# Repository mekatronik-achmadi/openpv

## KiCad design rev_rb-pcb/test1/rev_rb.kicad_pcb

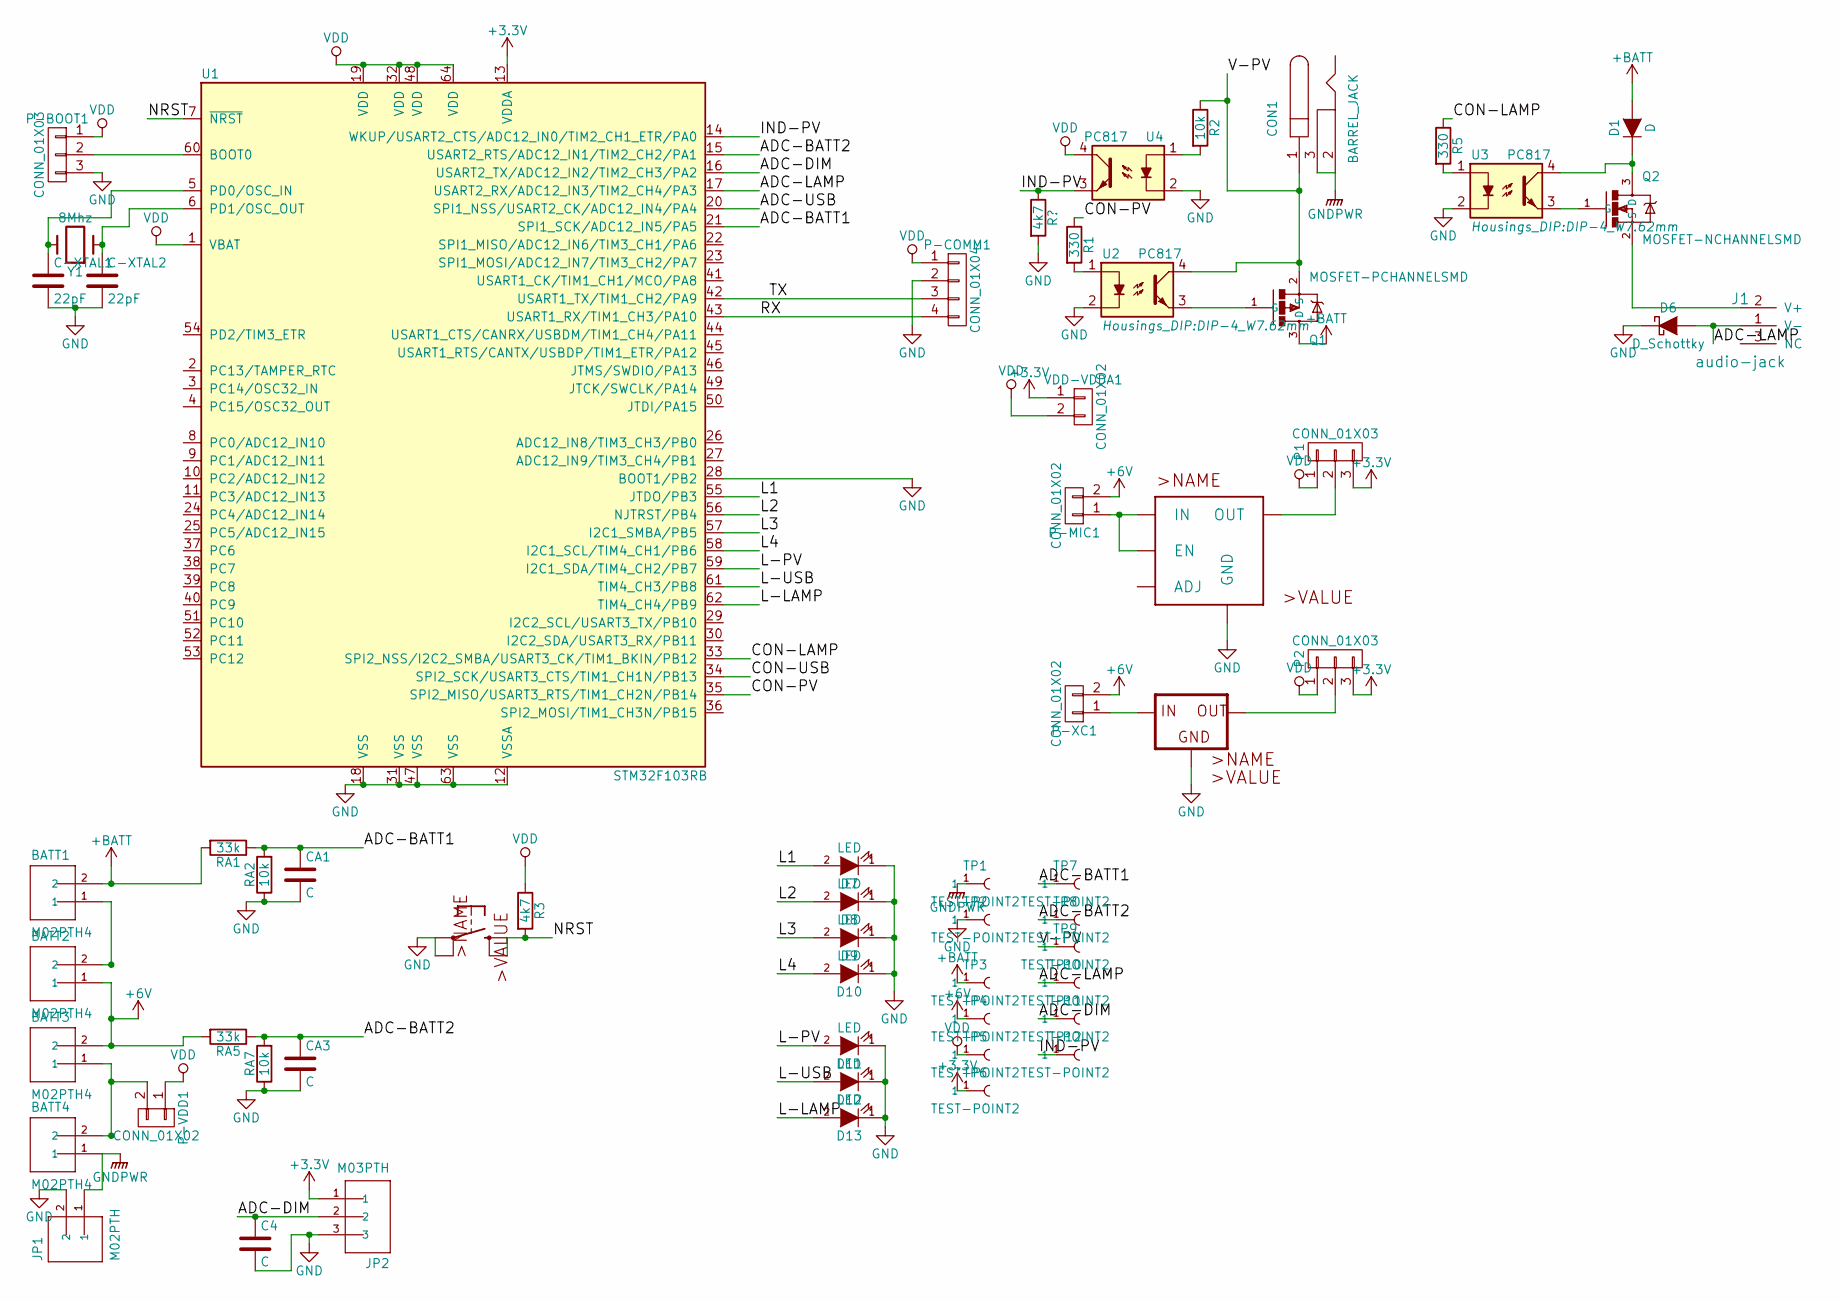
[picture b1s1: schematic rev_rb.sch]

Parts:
BATT1, BATT2, BATT3, BATT4: M02PTH4; SparkFun-1X02_XTRA_BIG
C4: C; C_0805
C-XTAL1, C-XTAL2: 22pF; C_0805
CA1, CA3: C; C_0805
CON1: BARREL_JACK; JACK_ALIM
D1: D; SMA_Standard
D6: D_Schottky; SMA_Standard
D7, D8, D9, D10, D11, D12, D13: LED; LED-0805
J1: audio-jack; JACK_LAPAN
JP1: M02PTH; SparkFun-1X02_XTRA_BIG
JP2: M03PTH; SparkFun-1X03_LONGPADS
P1, P2: CONN_01X03; Pin_Header_Straight_1x03
P-BOOT1: CONN_01X03; Pin_Header_Straight_1x03
P-COMM1: CONN_01X04; Pin_Header_Straight_1x04
P-MIC1: CONN_01X02; Pin_Header_Straight_1x02
P-VDD1: CONN_01X02; Pin_Header_Straight_1x02
P-XC1: CONN_01X02; Pin_Header_Straight_1x02
Q1: MOSFET-PCHANNELSMD; TO-220
Q2: MOSFET-NCHANNELSMD; TO-220
R1, R5: 330; R_0805
R2: 10k; R_0805
R3: 4k7; R_0805
RA1, RA5: 33k; R_0805
RA2, RA7: 10k; R_0805
TP1, TP2, TP3, TP4, TP5, TP6, TP7, TP8, TP9, TP10, TP11, TP12: TEST-POINT2; SparkFun-PAD.03X.05
U1: STM32F103RB; TQFP-64_10x10mm_Pitch0.5mm
U2, U3, U4: PC817; DIP-4_W7.62mm
U6: 10-XX_B3F-10XX; B3F-10XX
U7: MIC5219BM5_SOT23-5; SOT-23-5
U8: XC63FPM_SOT23; SOT-23
VDD-VDDA1: CONN_01X02; Pin_Header_Straight_1x02
Y1: 8Mhz; HC-49V

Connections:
+3V3: JP2.1, P1.3, P2.3, TP6.1, U1.13 (VDDA), VDD-VDDA1.1
+6V: BATT2.1, BATT3.2, P-MIC1.2, P-XC1.2, RA5.2, TP4.1
+BATT: BATT1.2, D1.2 (A), Q1.3 (D), RA1.2, TP3.1
/ADC-BATT1: CA1.1, RA1.1, RA2.2, TP7.1, U1.21 (SPI1_SCK/ADC12_IN5/PA5)
/ADC-BATT2: CA3.1, RA5.1, RA7.2, TP8.1, U1.15 (USART2_RTS/ADC12_IN1/TIM2_CH2/PA1)
/ADC-DIM: C4.1, JP2.2, TP11.1, U1.16 (USART2_TX/ADC12_IN2/TIM2_CH3/PA2)
/ADC-LAMP: D6.2 (A), J1.1 (V-), TP10.1, U1.17 (USART2_RX/ADC12_IN3/TIM2_CH4/PA3)
/ADC-USB: U1.20 (SPI1_NSS/USART2_CK/ADC12_IN4/PA4)
/CON-LAMP: R5.1, U1.33 (SPI2_NSS/I2C2_SMBA/USART3_CK/TIM1_BKIN/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)
/CON-PV: R1.1, U1.35 (SPI2_MISO/USART3_RTS/TIM1_CH2N/PB14)
/CON-USB: U1.34 (SPI2_SCK/USART3_CTS/TIM1_CH1N/PB13)
/IND-PV: TP12.1, U1.14 (WKUP/USART2_CTS/ADC12_IN0/TIM2_CH1_ETR/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), U4.3
/L1: D7.2 (A), U1.55 (JTDO/PB3)
/L2: D8.2 (A), U1.56 (NJTRST/PB4)
/L3: D9.2 (A), U1.57 (I2C1_SMBA/PB5)
/L4: D10.2 (A), U1.58 (I2C1_SCL/TIM4_CH1/PB6)
/L-LAMP: D13.2 (A), U1.62 (TIM4_CH4/PB9)
/L-PV: D11.2 (A), U1.59 (I2C1_SDA/TIM4_CH2/PB7)
/L-USB: D12.2 (A), U1.61 (TIM4_CH3/PB8)
/NRST: R3.2, U1.7 (~NRST), U6.1 (S), U6.2 (S1)
/RX: P-COMM1.4, U1.43 (USART1_RX/TIM1_CH3/PA10)
/TX: P-COMM1.3, U1.42 (USART1_TX/TIM1_CH2/PA9)
/V-PV: CON1.1, Q1.2 (S), R2.1, TP9.1, U2.4
GND: C4.2, C-XTAL1.2, C-XTAL2.2, CA1.2, CA3.2, D6.1 (K), D7.1 (K), D8.1 (K), D9.1 (K), D10.1 (K), D11.1 (K), D12.1 (K), D13.1 (K), JP1.2, JP2.3, P-BOOT1.3, P-COMM1.2, RA2.1, RA7.1, TP2.1, U1.12 (VSSA), U1.18 (VSS), U1.28 (BOOT1/PB2), U1.31 (VSS), U1.47 (VSS), U1.63 (VSS), U2.2, U3.2, U4.2, U6.3, U6.4 (P1), U7.2 (GND), U8.1 (GND)
GNDPWR: BATT4.1, CON1.2, CON1.3, JP1.1, TP1.1
unnamed: BATT1.1, BATT2.2
unnamed: BATT3.1, BATT4.2, P-VDD1.2
unnamed: C-XTAL1.1, U1.5 (PD0/OSC_IN), Y1.2
unnamed: C-XTAL2.1, U1.6 (PD1/OSC_OUT), Y1.1
unnamed: D1.1 (K), Q2.3 (D), U3.4
unnamed: J1.2 (V+), Q2.2 (S)
unnamed: P1.2, U7.5 (OUT)
unnamed: P2.2, U8.2 (OUT)
unnamed: P-BOOT1.2, U1.60 (BOOT0)
unnamed: P-MIC1.1, U7.1 (IN), U7.3 (EN)
unnamed: P-XC1.1, U8.3 (IN)
unnamed: Q1.1 (G), U2.3
unnamed: Q2.1 (G), U3.3
unnamed: R1.2, U2.1
unnamed: R2.2, U4.1
unnamed: R5.2, U3.1
VDD: P1.1, P2.1, P-BOOT1.1, P-COMM1.1, P-VDD1.1, R3.1, TP5.1, U1.1 (VBAT), U1.19 (VDD), U1.32 (VDD), U1.48 (VDD), U1.64 (VDD), U4.4, VDD-VDDA1.2

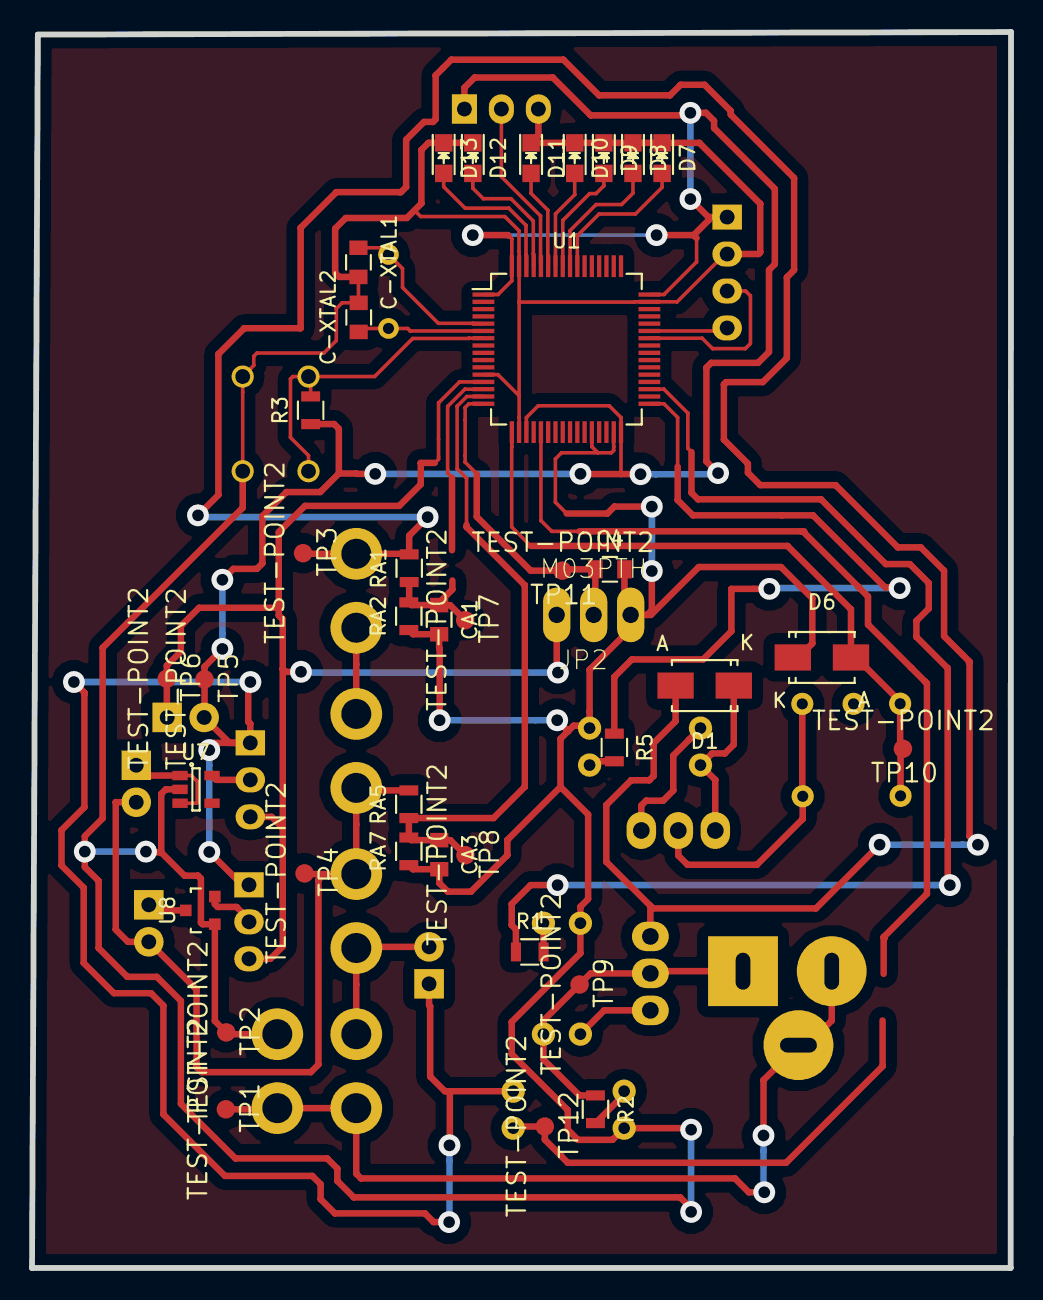
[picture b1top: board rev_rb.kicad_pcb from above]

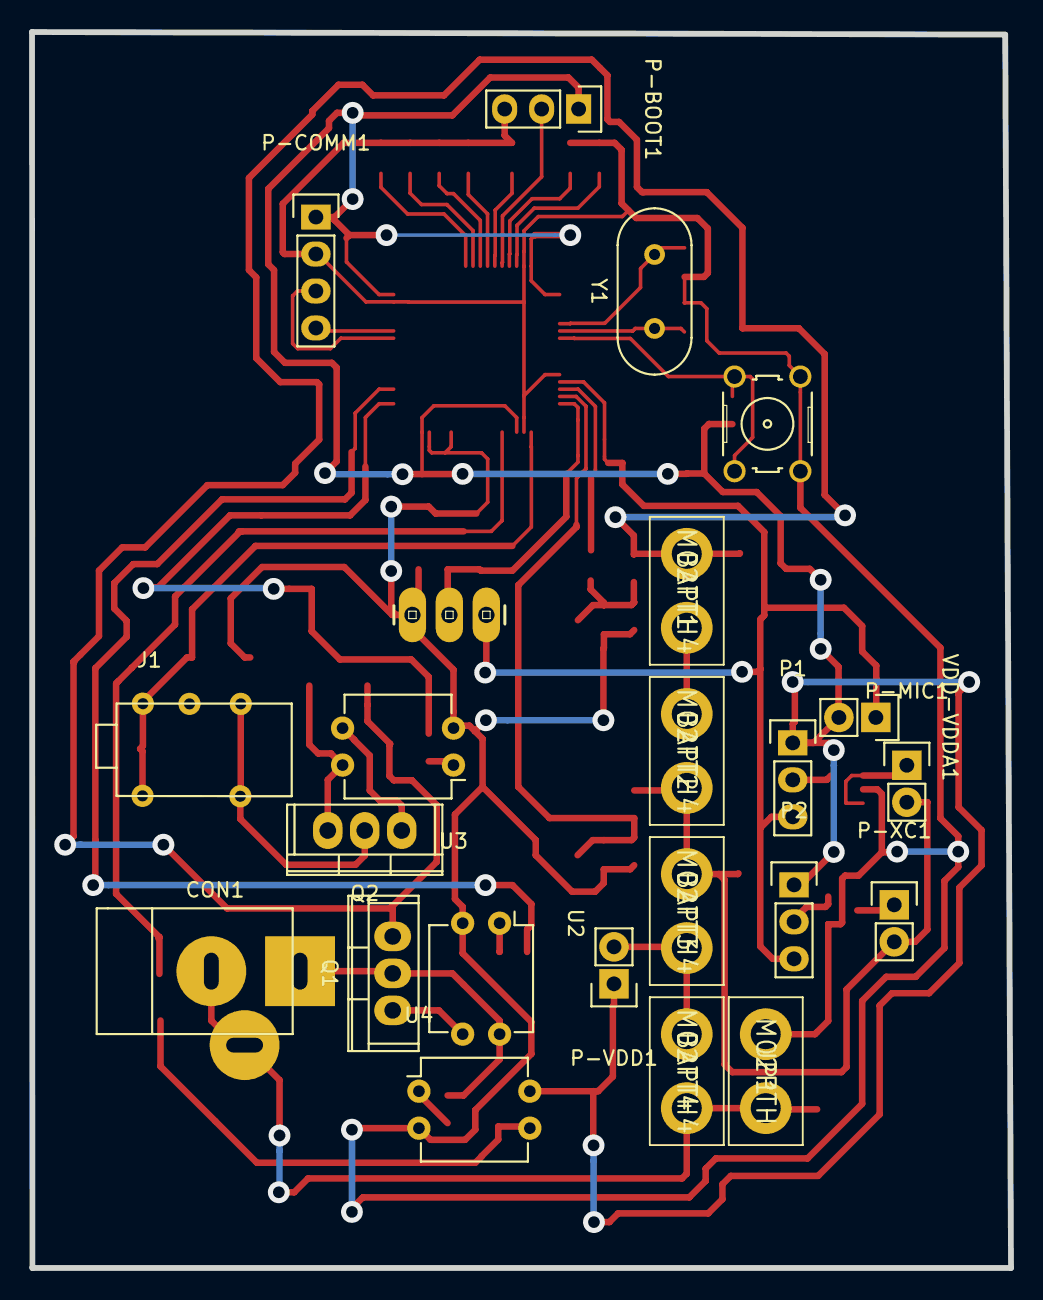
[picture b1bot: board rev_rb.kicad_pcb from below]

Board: 2 copper layers, 67.2 x 84.9 mm, 60 parts (23 on the bottom side), 40 nets.

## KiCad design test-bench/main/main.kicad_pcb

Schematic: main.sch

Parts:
C-REG1, C-REG2: 100uF 50v; C_Radial_D5_L6_P2.5
CON-REG1: BARREL_JACK; JACK_ALIM
D1, D2, D3, D4: LED; LED-3MM
D-REG1: D; Diode_DO-35_SOD27_Horizontal_RM10
D-RTC1, D-RTC2: D; Diode_DO-35_SOD27_Horizontal_RM10
DS-REG1: D_Schottky; Diode_DO-35_SOD27_Horizontal_RM10
DZ-REG1: 5v6; Diode_DO-35_SOD27_Horizontal_RM10
IC1: ATMEGA128-A; TQFP-64_14x14mm_Pitch0.8mm
L-REG1: INDUCTOR; INDUCTOR_V
P-ASP1: CONN_01X06; Pin_Header_Straight_1x06
P-LAMP1, P-LAMP2, P-LAMP3, P-LAMP4, P-LAMP5, P-LAMP6, P-LAMP7, P-LAMP8: CONN_02X08; Pin_Header_Straight_2x08
P-RTCBATT1: CONN_01X02; Pin_Header_Straight_1x02
P-UART1: CONN_01X04; Pin_Header_Straight_1x04
R-DISP1, R-DISP2, R-DISP3, R-DISP4, R-DISP5, R-DISP6, R-DISP7: 330; Resistor_Horizontal_RM10mm
R-LED1, R-LED2, R-LED3, R-LED4: 330; Resistor_Horizontal_RM10mm
R-RST1: 4k7; Resistor_Horizontal_RM10mm
R-RTC1, R-RTC2: 4k7; Resistor_Horizontal_RM10mm
U1: 4511N_DIL16; DIP-16_W7.62mm_LongPads
U2: LM2596S_TO263-5; TO-263-5Lead
U3: PCF8563; SOIJ-8_5.3x5.3mm_Pitch1.27mm
Y1: 32khz; Crystal_Watch

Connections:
/D1-A: IC1.61 (PF0(ADC0)), P-LAMP1.15
/D1-B: IC1.60 (PF1(ADC1)), P-LAMP1.13
/D1-C: IC1.59 (PF2(ADC2)), P-LAMP1.11
/D2-A: IC1.58 (PF3(ADC3)), P-LAMP2.15
/D2-B: IC1.57 (PF4(ADC4/TCK)), P-LAMP2.13
/D2-C: IC1.56 (PF5(ADC5/TMS)), P-LAMP2.11
/D3-A: IC1.7 (PE5(OC3C/INT5)), P-LAMP3.11
/D3-B: IC1.8 (PE6(T3/INT6)), P-LAMP3.13
/D3-C: IC1.9 (PE7(IC3/INT7)), P-LAMP3.15
/D4-A: IC1.47 ((AD4)PA4), P-LAMP4.15
/D4-B: IC1.46 ((AD5)PA5), P-LAMP4.13
/D4-C: IC1.45 ((AD6)PA6), P-LAMP4.11
/D5-A: IC1.44 ((AD7)PA7), P-LAMP5.15
/D5-B: IC1.43 (PG2(ALE)), P-LAMP5.13
/D5-C: IC1.42 ((A15)PC7), P-LAMP5.11
/D6-A: IC1.41 ((A14)PC6), P-LAMP6.15
/D6-B: IC1.40 ((A13)PC5), P-LAMP6.13
/D6-C: IC1.39 ((A12)PC4), P-LAMP6.11
/D6-D: IC1.38 ((A11)PC3), P-LAMP6.9
/D7-A: IC1.37 ((A10)PC2), P-LAMP7.15
/D7-B: IC1.36 ((A9)PC1), P-LAMP7.13
/D7-C: IC1.35 ((A8)PC0), P-LAMP7.11
/D7-D: IC1.34 (PG1(~RD~)), P-LAMP7.9
/D8-A: IC1.29 ((ICP1)PD4), P-LAMP8.9
/D8-B: IC1.30 ((XCK1)PD5), P-LAMP8.11
/D8-C: IC1.31 ((T1)PD6), P-LAMP8.13
/D8-D: IC1.32 ((T2)PD7), P-LAMP8.15
/IA: IC1.51 ((AD0)PA0), U1.7 (IA)
/IB: IC1.50 ((AD1)PA1), U1.1 (IB)
/IC: IC1.49 ((AD2)PA2), U1.2 (IC)
/ID: IC1.48 ((AD3)PA3), U1.6 (ID)
/LA: P-LAMP1.10, P-LAMP2.10, P-LAMP3.10, P-LAMP4.10, P-LAMP5.10, P-LAMP6.10, P-LAMP7.10, P-LAMP8.10, R-DISP1.1
/LB: P-LAMP1.8, P-LAMP2.8, P-LAMP3.8, P-LAMP4.8, P-LAMP5.8, P-LAMP6.8, P-LAMP7.8, P-LAMP8.8, R-DISP2.1
/LC: P-LAMP1.6, P-LAMP2.6, P-LAMP3.6, P-LAMP4.6, P-LAMP5.6, P-LAMP6.6, P-LAMP7.6, P-LAMP8.6, R-DISP3.1
/LD: P-LAMP1.4, P-LAMP2.4, P-LAMP3.4, P-LAMP4.4, P-LAMP5.4, P-LAMP6.4, P-LAMP7.4, P-LAMP8.4, R-DISP4.1
/LE: P-LAMP1.2, P-LAMP2.2, P-LAMP3.2, P-LAMP4.2, P-LAMP5.2, P-LAMP6.2, P-LAMP7.2, P-LAMP8.2, R-DISP5.1
/LF: P-LAMP1.14, P-LAMP2.14, P-LAMP3.14, P-LAMP4.14, P-LAMP5.14, P-LAMP6.14, P-LAMP7.14, P-LAMP8.14, R-DISP6.1
/LG: P-LAMP1.12, P-LAMP2.12, P-LAMP3.12, P-LAMP4.12, P-LAMP5.12, P-LAMP6.12, P-LAMP7.12, P-LAMP8.12, R-DISP7.1
/MISO: IC1.2 (PE0(RXD0/PDI)), P-ASP1.6
/MOSI: IC1.3 (PE1(TXD0/PDO)), P-ASP1.5
/RST: IC1.20 (~RESET), P-ASP1.3, R-RST1.2
/RTC-SCL: IC1.25 ((SCL/INT0)PD0), R-RTC2.2, U3.6 (SCL)
/RTC-SDA: IC1.26 ((SDA/INT1)PD1), R-RTC1.2, U3.5 (SDA)
/RUN: D2.1 (K), IC1.10 ((~SS~)PB0)
/RX: D3.1 (K), IC1.28 ((TXD1/INT3)PD3), P-UART1.3
/SCK: IC1.11 ((SCK)PB1), P-ASP1.4
/TX: D4.1 (K), IC1.27 ((RXD1/INT2)PD2), P-UART1.4
GND: C-REG1.2, C-REG2.2, CON-REG1.2, CON-REG1.3, D1.1 (K), DS-REG1.2 (A), DZ-REG1.2 (A), IC1.22 (GND), IC1.53 (GND), IC1.63 (AGND), P-ASP1.2, P-LAMP1.16, P-LAMP2.16, P-LAMP3.16, P-LAMP4.16, P-LAMP5.16, P-LAMP6.16, P-LAMP7.16, P-LAMP8.16, P-RTCBATT1.2, P-UART1.2, U1.5 (LE), U1.8 (VSS), U2.3 (GND), U2.5 (!ON!/OFF), U3.4 (VSS)
unnamed: C-REG1.1, D-REG1.1 (K), U2.1 (VIN)
unnamed: CON-REG1.1, D-REG1.2 (A)
unnamed: D1.2 (A), R-LED1.2
unnamed: D2.2 (A), R-LED2.2
unnamed: D3.2 (A), R-LED3.2
unnamed: D4.2 (A), R-LED4.2
unnamed: D-RTC1.1 (K), D-RTC2.1 (K), U3.8 (VDD)
unnamed: D-RTC2.2 (A), P-RTCBATT1.1
unnamed: DS-REG1.1 (K), L-REG1.2, U2.2 (OUT)
unnamed: R-DISP1.2, U1.13 (A)
unnamed: R-DISP2.2, U1.12 (B)
unnamed: R-DISP3.2, U1.11 (C)
unnamed: R-DISP4.2, U1.10 (D)
unnamed: R-DISP5.2, U1.9 (E)
unnamed: R-DISP6.2, U1.15 (F)
unnamed: R-DISP7.2, U1.14 (G)
unnamed: U3.1 (OSCI), Y1.1
unnamed: U3.2 (OSCO), Y1.2
VCC: C-REG2.1, D-RTC1.2 (A), DZ-REG1.1 (K), IC1.21 (VCC), IC1.52 (VCC), IC1.64 (AVCC), L-REG1.1, P-ASP1.1, P-LAMP1.1, P-LAMP2.1, P-LAMP3.1, P-LAMP4.1, P-LAMP5.1, P-LAMP6.1, P-LAMP7.1, P-LAMP8.1, P-UART1.1, R-LED1.1, R-LED2.1, R-LED3.1, R-LED4.1, R-RST1.1, R-RTC1.1, R-RTC2.1, U1.3 (LT), U1.4 (BI), U1.16 (VDD), U2.4 (FB)

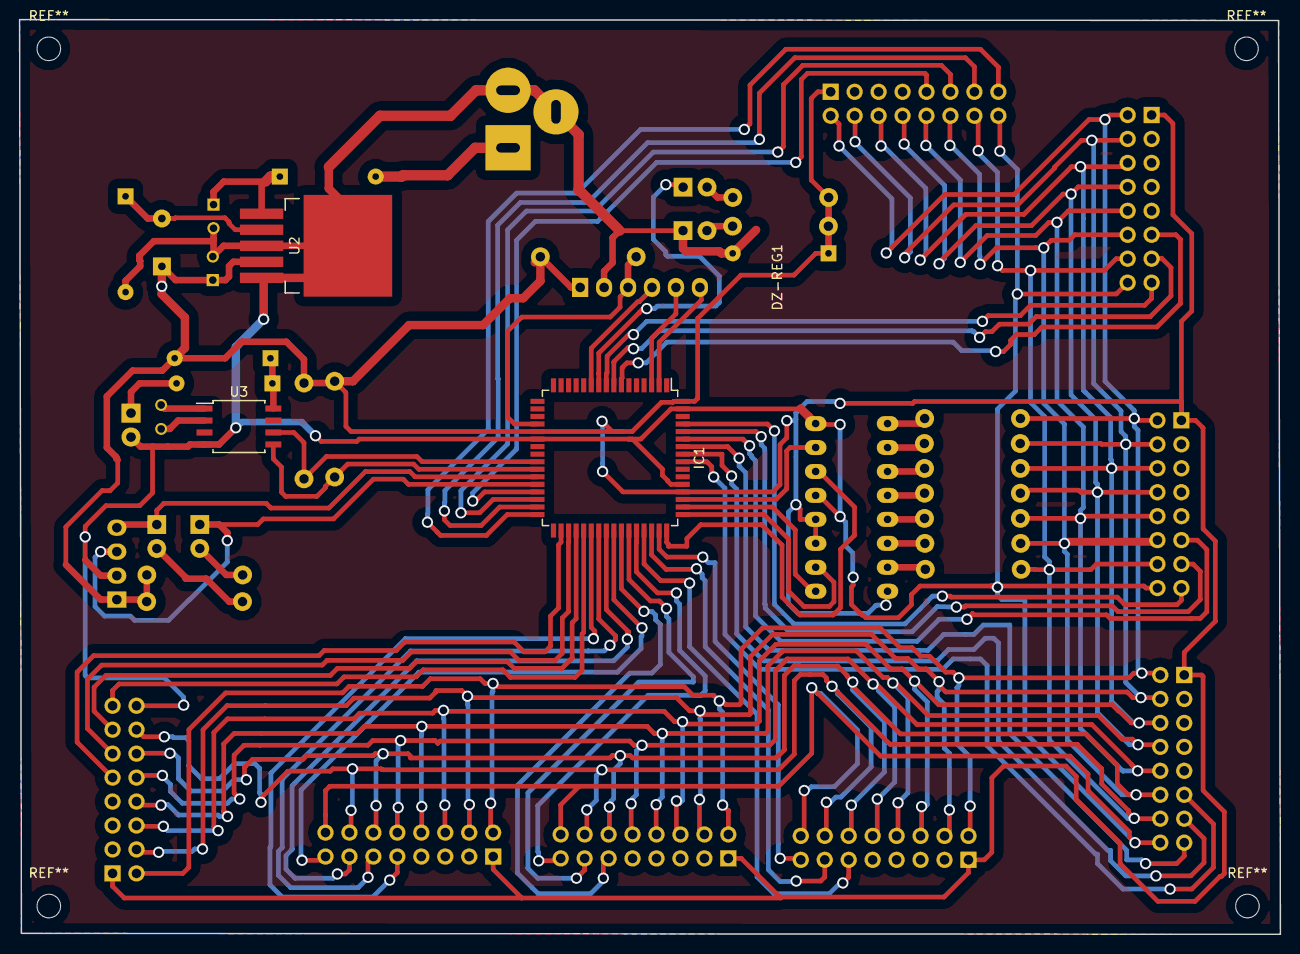
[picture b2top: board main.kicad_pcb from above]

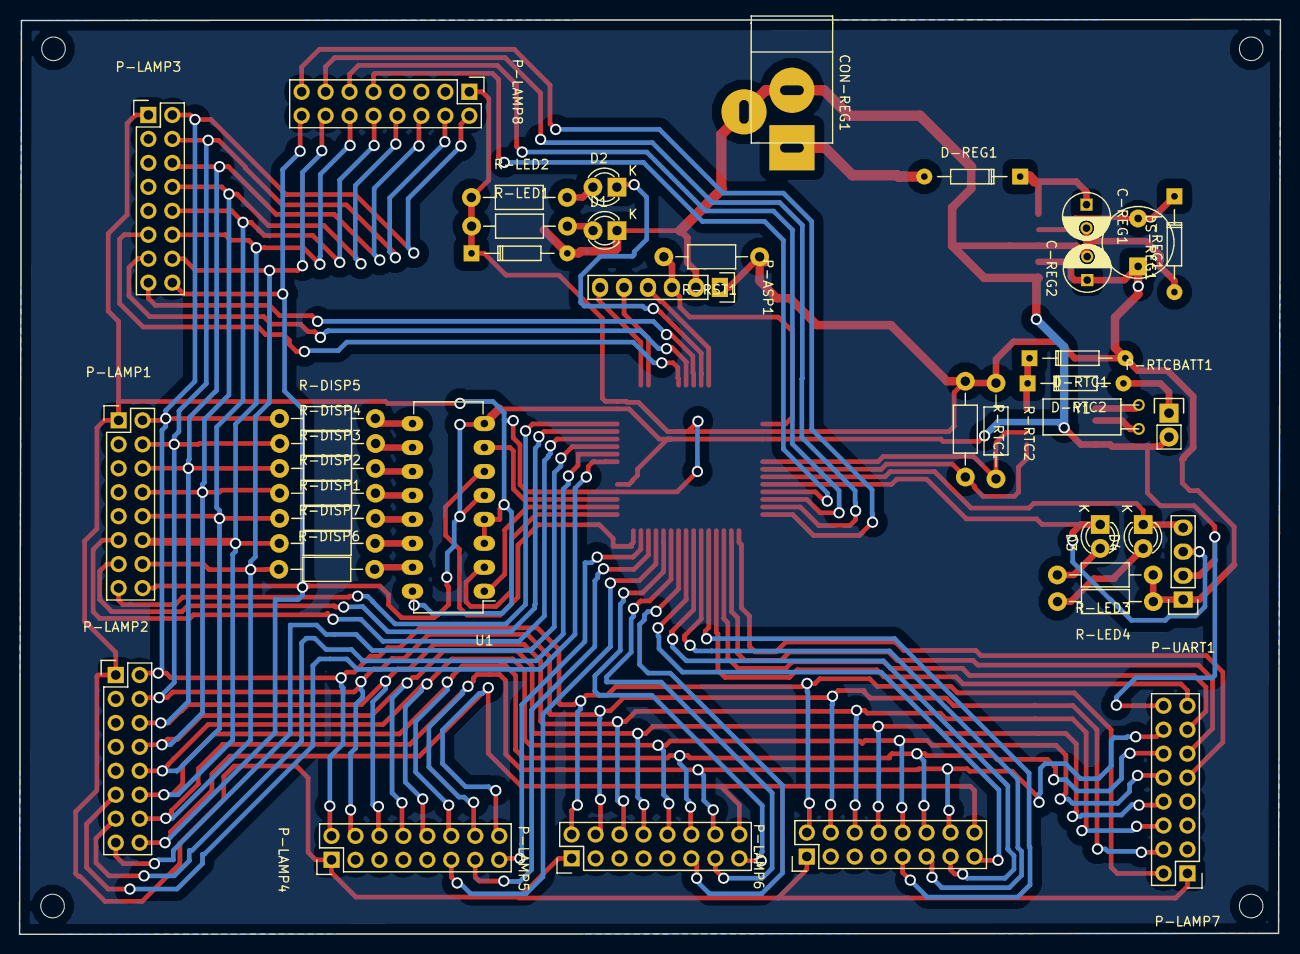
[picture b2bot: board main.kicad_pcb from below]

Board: 2 copper layers, 133.7 x 97.0 mm, 43 parts (40 on the bottom side), 67 nets.

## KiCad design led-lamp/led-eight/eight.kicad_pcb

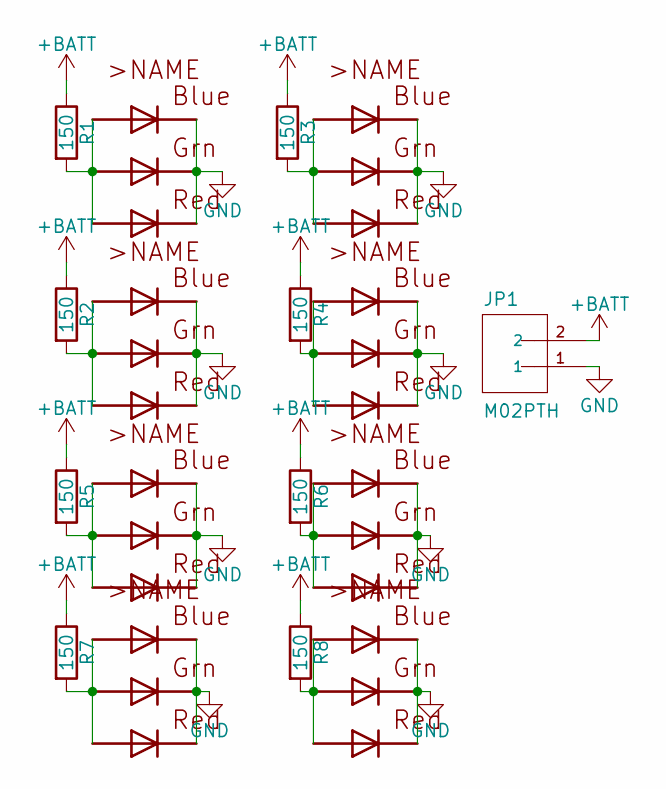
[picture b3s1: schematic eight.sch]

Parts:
JP1: M02PTH; SparkFun-1X02_XTRA_BIG
R1, R2, R3, R4, R5, R6, R7, R8: 150; Resistor_Horizontal_RM10mm
U1, U2, U3, U4, U5, U6, U7, U8: RGBLED5050_RGBLED5050; RGBLED5050

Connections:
+BATT: JP1.2, R1.1, R2.1, R3.1, R4.1, R5.1, R6.1, R7.1, R8.1
GND: JP1.1, U1.4 (BLUE_C), U1.5 (RED_C), U1.6 (GREEN_C), U2.4 (BLUE_C), U2.5 (RED_C), U2.6 (GREEN_C), U3.4 (BLUE_C), U3.5 (RED_C), U3.6 (GREEN_C), U4.4 (BLUE_C), U4.5 (RED_C), U4.6 (GREEN_C), U5.4 (BLUE_C), U5.5 (RED_C), U5.6 (GREEN_C), U6.4 (BLUE_C), U6.5 (RED_C), U6.6 (GREEN_C), U7.4 (BLUE_C), U7.5 (RED_C), U7.6 (GREEN_C), U8.4 (BLUE_C), U8.5 (RED_C), U8.6 (GREEN_C)
unnamed: R1.2, U1.1 (GREEN_A), U1.2 (RED_A), U1.3 (BLUE_A)
unnamed: R2.2, U2.1 (GREEN_A), U2.2 (RED_A), U2.3 (BLUE_A)
unnamed: R3.2, U3.1 (GREEN_A), U3.2 (RED_A), U3.3 (BLUE_A)
unnamed: R4.2, U4.1 (GREEN_A), U4.2 (RED_A), U4.3 (BLUE_A)
unnamed: R5.2, U6.1 (GREEN_A), U6.2 (RED_A), U6.3 (BLUE_A)
unnamed: R6.2, U5.1 (GREEN_A), U5.2 (RED_A), U5.3 (BLUE_A)
unnamed: R7.2, U7.1 (GREEN_A), U7.2 (RED_A), U7.3 (BLUE_A)
unnamed: R8.2, U8.1 (GREEN_A), U8.2 (RED_A), U8.3 (BLUE_A)

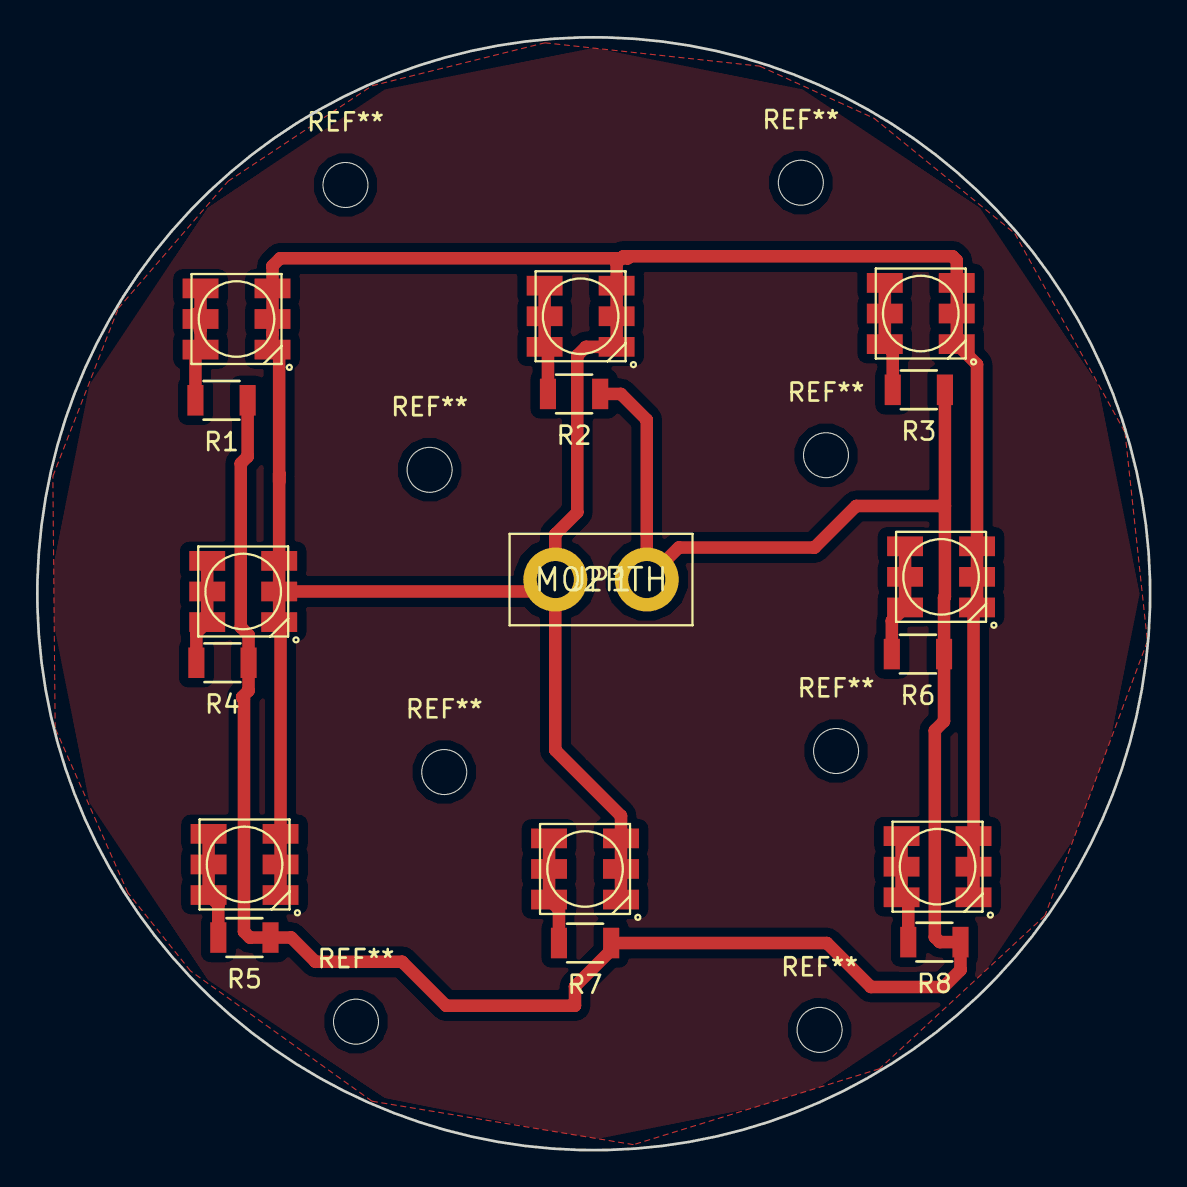
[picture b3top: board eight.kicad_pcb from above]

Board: 2 copper layers, 61.8 x 61.8 mm, 17 parts (0 on the bottom side), 10 nets.

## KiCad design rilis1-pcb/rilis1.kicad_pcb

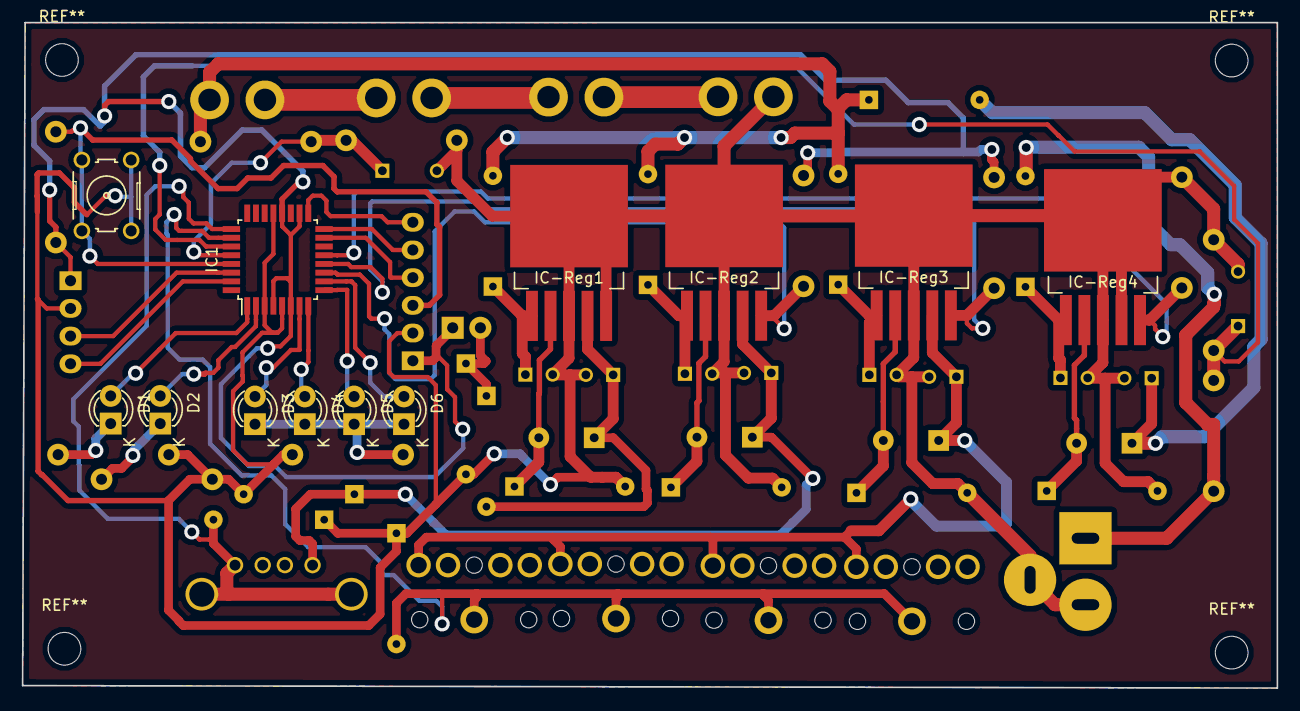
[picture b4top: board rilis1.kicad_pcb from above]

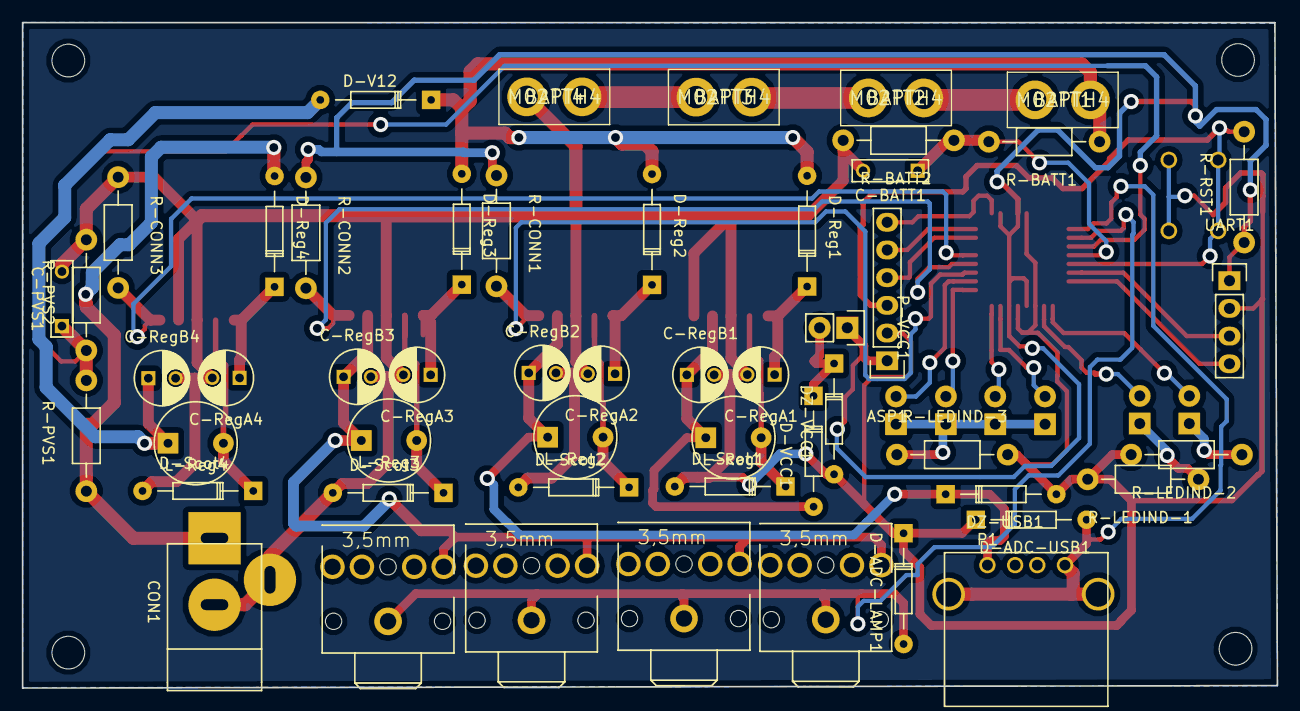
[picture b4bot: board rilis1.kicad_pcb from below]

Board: 2 copper layers, 115.1 x 61.0 mm, 64 parts (52 on the bottom side), 42 nets.

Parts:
ASP1: CONN_01X06; Pin_Header_Straight_1x06
BATT1, BATT2, BATT3, BATT4: M02PTH4; SparkFun-1X02_XTRA_BIG
C-BATT1: C; C_Rect_L7_W2_P5
C-PVS1: C; C_Rect_L7_W2_P5
C-RegA1, C-RegA2, C-RegA3, C-RegA4: CP; C_Radial_D5_L6_P2.5
C-RegB1, C-RegB2, C-RegB3, C-RegB4: CP; C_Radial_D5_L6_P2.5
CON1: BARREL_JACK; JACK_ALIM
D1, D2, D3, D4, D5, D6: LED; LED-3MM
D-ADC-LAMP1: D_Schottky; Diode_DO-35_SOD27_Horizontal_RM10
D-ADC-USB1: D_Schottky; Diode_DO-35_SOD27_Horizontal_RM10
D-Reg1, D-Reg2, D-Reg3, D-Reg4: D; Diode_DO-35_SOD27_Horizontal_RM10
D-Scot1, D-Scot2, D-Scot3, D-Scot4: D_Schottky; Diode_DO-35_SOD27_Horizontal_RM10
D-V12: D; Diode_DO-35_SOD27_Horizontal_RM10
D-VCC1: D_Schottky; Diode_DO-35_SOD27_Horizontal_RM10
DZ-USB1: 5v6; Diode_DO-35_SOD27_Horizontal_RM10
DZ-VCC1: 5v1; Diode_DO-35_SOD27_Horizontal_RM10
IC1: ATMEGA8A-A; TQFP-32_7x7mm_Pitch0.8mm
IC-Reg1, IC-Reg2: LM2596S-5v; TO-263-5Lead
IC-Reg3: LM2596S-12v; TO-263-5Lead
IC-Reg4: LM2596S-Adj; TO-263-5Lead
L-Reg1, L-Reg2, L-Reg3, L-Reg4: INDUCTOR; INDUCTOR_V
P1: USB_A
P-VCC1: CONN_01X02; Pin_Header_Straight_1x02
R-BATT1, R-BATT2: R; Resistor_Horizontal_RM10mm
R-CONN1, R-CONN2, R-CONN3: 4k7; Resistor_Horizontal_RM10mm
R-LEDIND-1, R-LEDIND-2, R-LEDIND-3: 330; Resistor_Horizontal_RM10mm
R-PVS1, R-PVS2: R; Resistor_Horizontal_RM10mm
R-RST1: 4k7; Resistor_Horizontal_RM10mm
S-RST1: 10-XX; B3F-10XX
U1, U2, U3, U4: STEREOJACK_STX3100; STX3100
UART1: CONN_01X04; Pin_Header_Straight_1x04

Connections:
+12V: BATT1.1, D-Reg1.2, D-Reg2.2, D-Reg3.2, D-V12.1, R-BATT1.1
/ADC-BATT: C-BATT1.1, IC1.28, R-BATT1.2, R-BATT2.1
/ADC-LAMP: D-ADC-LAMP1.2, IC1.26, U1.1, U2.1, U3.1, U4.1
/ADC-PV: C-PVS1.1, IC1.27, R-PVS1.2, R-PVS2.1
/ADC-USB: D-ADC-USB1.2, IC1.25, P1.4, P1.5
/CONN-LAMP: IC1.12, IC-Reg3.5, R-CONN2.2
/CONN-PV: IC1.13, IC-Reg4.5, R-CONN3.2
/CONN-USB: IC1.11, IC-Reg2.5, R-CONN1.2
/L1: D3.2, IC1.7
/L2: D4.2, IC1.8
/L3: D5.2, IC1.9
/L4: D6.2, IC1.10
/L-IN: D1.2, IC1.1
/L-OUT: D2.2, IC1.2
/NRST: ASP1.3, IC1.29, R-RST1.2, S-RST1.1, S-RST1.2
/PV-IN: CON1.1, D-Reg4.2, R-PVS1.1
GND: ASP1.2, BATT4.2, C-BATT1.2, C-PVS1.2, C-RegA1.2, C-RegA2.2, C-RegA3.2, C-RegA4.2, C-RegB1.2, C-RegB2.2, C-RegB3.2, C-RegB4.2, CON1.2, CON1.3, D-ADC-LAMP1.1, D-ADC-USB1.1, D-Scot1.2, D-Scot2.2, D-Scot3.2, D-Scot4.2, DZ-USB1.2, DZ-VCC1.2, IC1.3, IC1.5, IC1.21, IC-Reg1.3, IC-Reg1.5, IC-Reg2.3, IC-Reg3.3, IC-Reg4.3, IC-Reg4.4, R-BATT2.2, R-CONN3.1, R-LEDIND-1.2, R-LEDIND-2.2, R-LEDIND-3.2, R-PVS2.2, S-RST1.3, S-RST1.4, UART1.2
unnamed: ASP1.4, IC1.15
unnamed: ASP1.5, IC1.16
unnamed: ASP1.6, IC1.17
unnamed: BATT1.2, BATT2.1
unnamed: BATT2.2, BATT3.1
unnamed: BATT3.2, BATT4.1
unnamed: C-RegA1.1, D-Reg1.1, IC-Reg1.1
unnamed: C-RegA2.1, D-Reg2.1, IC-Reg2.1
unnamed: C-RegA3.1, D-Reg3.1, IC-Reg3.1
unnamed: C-RegA4.1, D-Reg4.1, IC-Reg4.1
unnamed: C-RegB1.1, D-VCC1.2, IC-Reg1.4, L-Reg1.1
unnamed: C-RegB2.1, DZ-USB1.1, IC-Reg2.4, L-Reg2.1, P1.1
unnamed: C-RegB3.1, IC-Reg3.4, L-Reg3.1, U1.5, U2.5, U3.5, U4.5
unnamed: C-RegB4.1, D-V12.2, L-Reg4.1
unnamed: D1.1, R-LEDIND-2.1
unnamed: D2.1, R-LEDIND-1.1
unnamed: D3.1, D4.1, D5.1, D6.1, R-LEDIND-3.1
unnamed: D-Scot1.1, IC-Reg1.2, L-Reg1.2
unnamed: D-Scot2.1, IC-Reg2.2, L-Reg2.2
unnamed: D-Scot3.1, IC-Reg3.2, L-Reg3.2
unnamed: D-Scot4.1, IC-Reg4.2, L-Reg4.2
unnamed: D-VCC1.1, DZ-VCC1.1, P-VCC1.2
unnamed: IC1.30, UART1.3
unnamed: IC1.31, UART1.4
VCC: ASP1.1, IC1.4, IC1.6, IC1.18, IC1.20, P-VCC1.1, R-CONN1.1, R-CONN2.1, R-RST1.1, UART1.1

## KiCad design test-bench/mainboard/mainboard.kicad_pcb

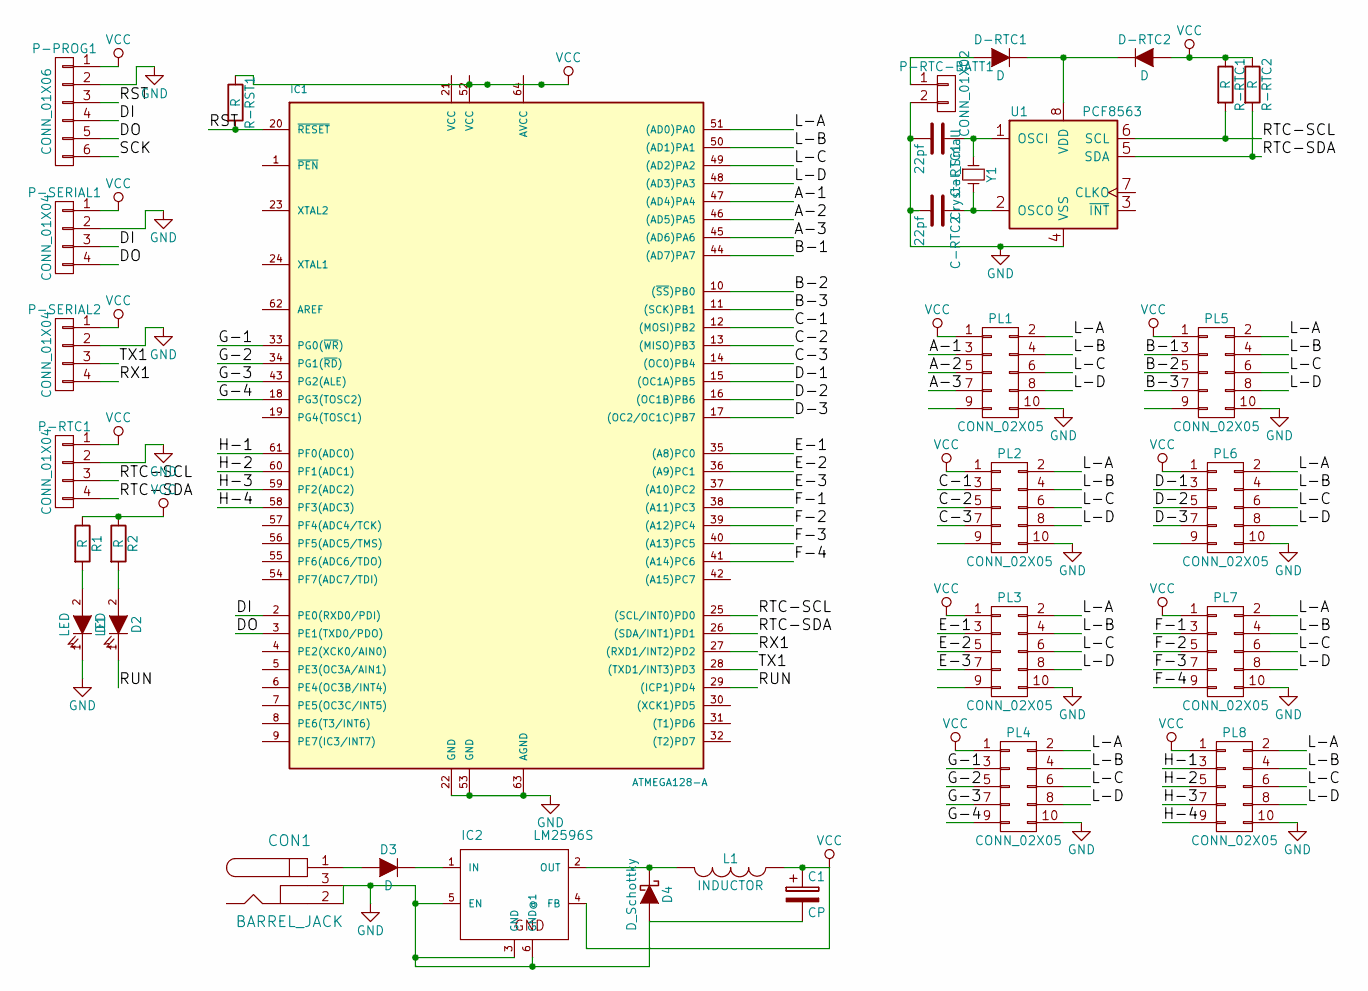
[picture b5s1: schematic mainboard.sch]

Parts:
C1: CP; C_Radial_D5_L6_P2.5
C-RTC1, C-RTC2: 22pf; C_Disc_D3_P2.5
CON1: BARREL_JACK; JACK_ALIM
D1, D2: LED; LED-3MM
D3: D; Diode_DO-35_SOD27_Horizontal_RM10
D4: D_Schottky; Diode_DO-35_SOD27_Horizontal_RM10
D-RTC1, D-RTC2: D; Diode_DO-35_SOD27_Horizontal_RM10
IC1: ATMEGA128-A; LQFP-64_14x14mm_Pitch0.8mm
IC2: LM2596S; TO-263-5Lead
L1: INDUCTOR; INDUCTOR_V
P-PROG1: CONN_01X06; Pin_Header_Straight_1x06
P-RTC1: CONN_01X04; Pin_Header_Straight_1x04
P-RTC-BATT1: CONN_01X02; Pin_Header_Straight_1x02
P-SERIAL1, P-SERIAL2: CONN_01X04; Pin_Header_Straight_1x04
PL1, PL2, PL3, PL4, PL5, PL6, PL7, PL8: CONN_02X05; Pin_Header_Straight_2x05
R1, R2: R; Resistor_Horizontal_RM10mm
R-RST1: R; Resistor_Horizontal_RM10mm
R-RTC1, R-RTC2: R; Resistor_Horizontal_RM10mm
U1: PCF8563; SOIC-8_3.9x4.9mm_Pitch1.27mm
Y1: Crystal_Small; Crystal_Watch

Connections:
/A-1: IC1.47 ((AD4)PA4), PL1.3
/A-2: IC1.46 ((AD5)PA5), PL1.5
/A-3: IC1.45 ((AD6)PA6), PL1.7
/B-1: IC1.44 ((AD7)PA7), PL5.3
/B-2: IC1.10 ((~SS~)PB0), PL5.5
/B-3: IC1.11 ((SCK)PB1), PL5.7
/C-1: IC1.12 ((MOSI)PB2), PL2.3
/C-2: IC1.13 ((MISO)PB3), PL2.5
/C-3: IC1.14 ((OC0)PB4), PL2.7
/D-1: IC1.15 ((OC1A)PB5), PL6.3
/D-2: IC1.16 ((OC1B)PB6), PL6.5
/D-3: IC1.17 ((OC2/OC1C)PB7), PL6.7
/DI: IC1.2 (PE0(RXD0/PDI)), P-PROG1.4, P-SERIAL1.3
/DO: IC1.3 (PE1(TXD0/PDO)), P-PROG1.5, P-SERIAL1.4
/E-1: IC1.35 ((A8)PC0), PL3.3
/E-2: IC1.36 ((A9)PC1), PL3.5
/E-3: IC1.37 ((A10)PC2), PL3.7
/F-1: IC1.38 ((A11)PC3), PL7.3
/F-2: IC1.39 ((A12)PC4), PL7.5
/F-3: IC1.40 ((A13)PC5), PL7.7
/F-4: IC1.41 ((A14)PC6), PL7.9
/G-1: IC1.33 (PG0(~WR~)), PL4.3
/G-2: IC1.34 (PG1(~RD~)), PL4.5
/G-3: IC1.43 (PG2(ALE)), PL4.7
/G-4: IC1.18 (PG3(TOSC2)), PL4.9
/H-1: IC1.61 (PF0(ADC0)), PL8.3
/H-2: IC1.60 (PF1(ADC1)), PL8.5
/H-3: IC1.59 (PF2(ADC2)), PL8.7
/H-4: IC1.58 (PF3(ADC3)), PL8.9
/L-A: IC1.51 ((AD0)PA0), PL1.2, PL2.2, PL3.2, PL4.2, PL5.2, PL6.2, PL7.2, PL8.2
/L-B: IC1.50 ((AD1)PA1), PL1.4, PL2.4, PL3.4, PL4.4, PL5.4, PL6.4, PL7.4, PL8.4
/L-C: IC1.49 ((AD2)PA2), PL1.6, PL2.6, PL3.6, PL4.6, PL5.6, PL6.6, PL7.6, PL8.6
/L-D: IC1.48 ((AD3)PA3), PL1.8, PL2.8, PL3.8, PL4.8, PL5.8, PL6.8, PL7.8, PL8.8
/RST: IC1.20 (~RESET), P-PROG1.3, R-RST1.2
/RTC-SCL: IC1.25 ((SCL/INT0)PD0), P-RTC1.3, R-RTC1.2, U1.6 (SCL)
/RTC-SDA: IC1.26 ((SDA/INT1)PD1), P-RTC1.4, R-RTC2.2, U1.5 (SDA)
/RUN: D2.1 (K), IC1.29 ((ICP1)PD4)
/RX1: IC1.27 ((RXD1/INT2)PD2), P-SERIAL2.4
/SCK: P-PROG1.6
/TX1: IC1.28 ((TXD1/INT3)PD3), P-SERIAL2.3
GND: C1.2, C-RTC1.2, C-RTC2.2, CON1.2, CON1.3, D1.1 (K), D4.2 (A), IC1.22 (GND), IC1.53 (GND), IC1.63 (AGND), IC2.3 (GND), IC2.5 (EN), IC2.6 (GND@1), P-PROG1.2, P-RTC1.2, P-RTC-BATT1.2, P-SERIAL1.2, P-SERIAL2.2, PL1.10, PL2.10, PL3.10, PL4.10, PL5.10, PL6.10, PL7.10, PL8.10, U1.4 (VSS)
unnamed: C-RTC1.1, U1.1 (OSCI), Y1.1
unnamed: C-RTC2.1, U1.2 (OSCO), Y1.2
unnamed: CON1.1, D3.2 (A)
unnamed: D1.2 (A), R1.2
unnamed: D2.2 (A), R2.2
unnamed: D3.1 (K), IC2.1 (IN)
unnamed: D4.1 (K), IC2.2 (OUT), L1.2
unnamed: D-RTC1.1 (K), D-RTC2.1 (K), U1.8 (VDD)
unnamed: D-RTC1.2 (A), P-RTC-BATT1.1
VCC: C1.1, D-RTC2.2 (A), IC2.4 (FB), L1.1, P-PROG1.1, P-RTC1.1, P-SERIAL1.1, P-SERIAL2.1, PL1.1, PL2.1, PL3.1, PL4.1, PL5.1, PL6.1, PL7.1, PL8.1, R1.1, R2.1, R-RST1.1, R-RTC1.1, R-RTC2.1

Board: 2 copper layers, 33 parts (0 on the bottom side), 50 nets, no tracks yet.
